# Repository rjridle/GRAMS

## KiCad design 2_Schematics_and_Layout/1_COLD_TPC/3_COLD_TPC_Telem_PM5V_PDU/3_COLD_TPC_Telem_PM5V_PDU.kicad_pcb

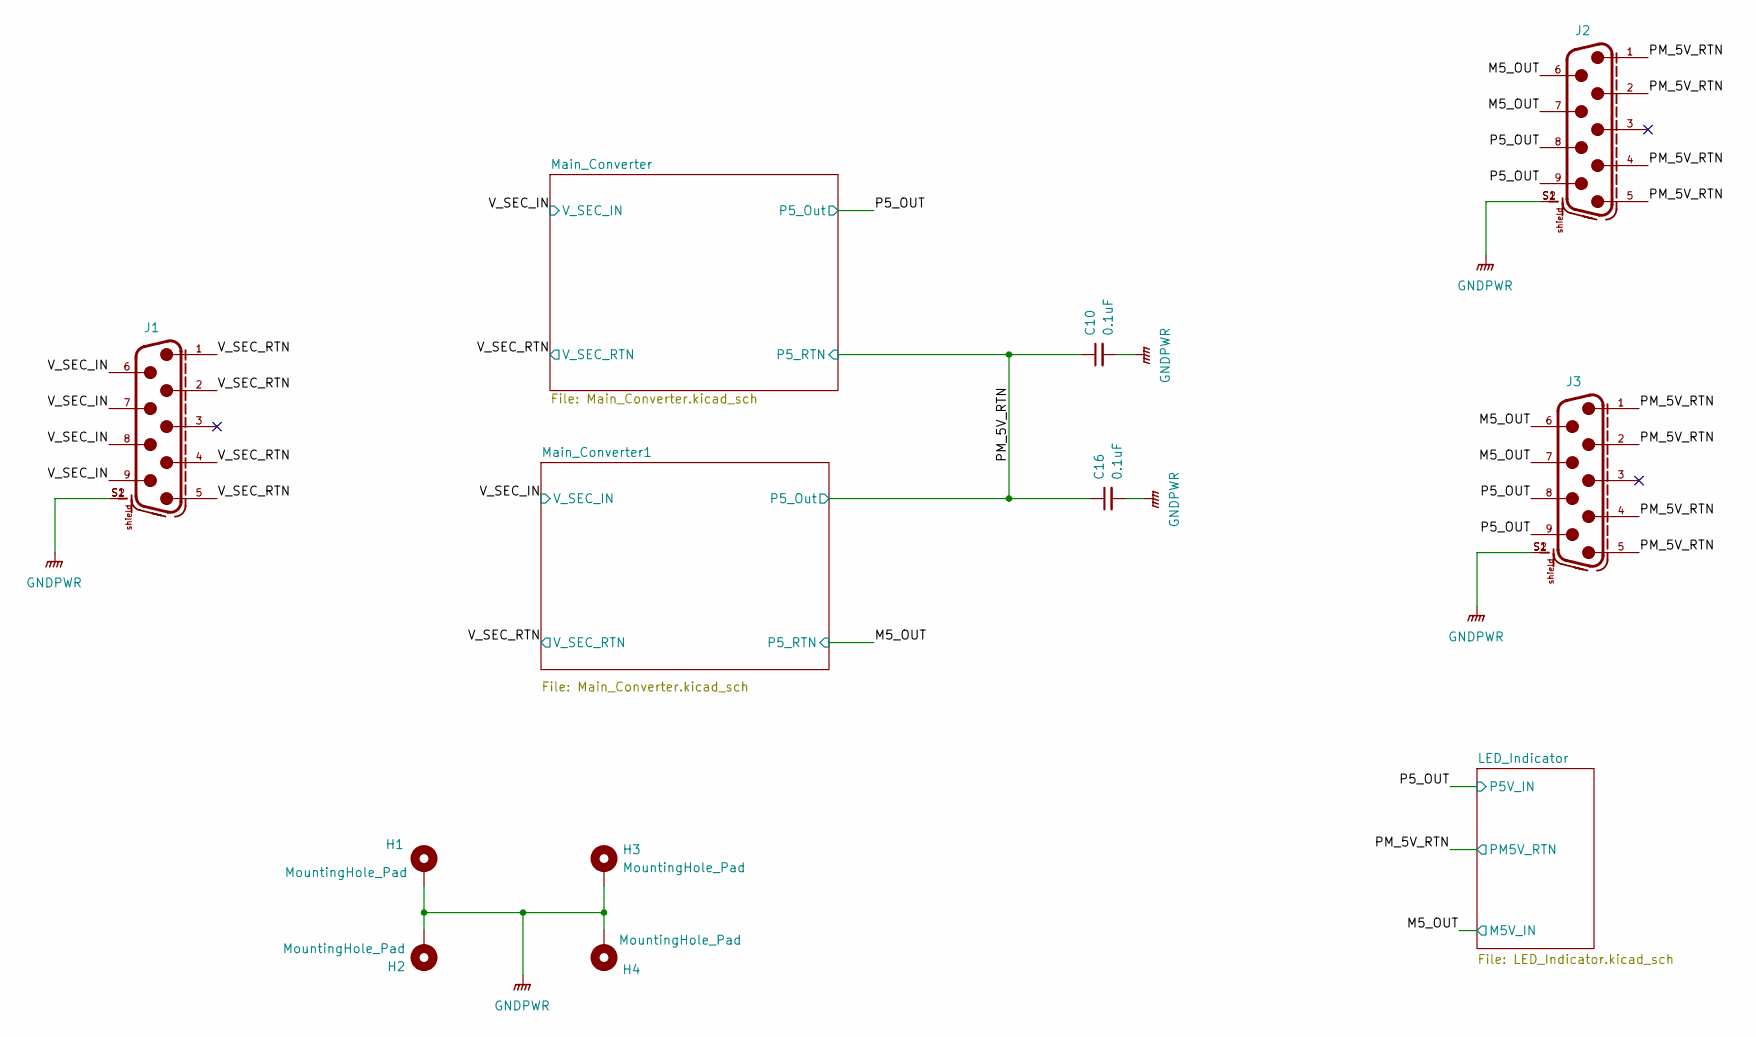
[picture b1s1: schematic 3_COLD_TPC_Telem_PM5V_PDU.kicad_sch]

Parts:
C10, C16: 0.1uF; C_0603_1608Metric; Man. Part Num CC0603KRX7R7BB104
H1, H2, H3, H4: MountingHole_Pad; MountingHole_3.2mm_M3_Pad
J1, J2, J3: 618009231221; PART-NUMBER 618009231221

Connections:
/M5_OUT: J2.6, J2.7, J3.6, J3.7; also elsewhere on the board
/P5_OUT: J2.8, J2.9, J3.8, J3.9; also elsewhere on the board
/PM_5V_RTN: C10.1, C16.1, J2.1, J2.2, J2.4, J2.5, J3.1, J3.2, J3.4, J3.5; also elsewhere on the board
/V_SEC_IN: J1.6, J1.7, J1.8, J1.9; also elsewhere on the board
/V_SEC_RTN: J1.1, J1.2, J1.4, J1.5; also elsewhere on the board
GNDPWR: C10.2, C16.2, H1.1, H2.1, H3.1, H4.1, J1.S1, J1.S2, J2.S1, J2.S2, J3.S1, J3.S2

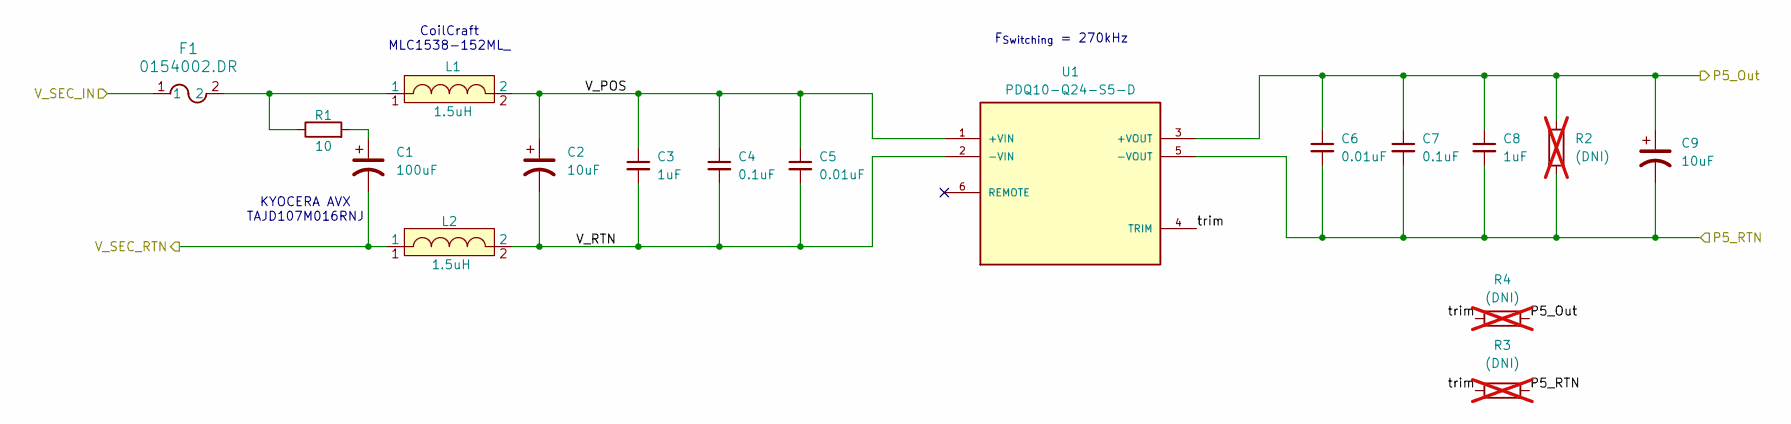
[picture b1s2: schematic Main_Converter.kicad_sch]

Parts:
C1: 100uF; CP_EIA-7343-20_Kemet-V; Man. Part Num TAJD107K020RNJ
C2: 10uF; CP_EIA-3216-12_Kemet-S; Man. Part Num TAJA106K016RNJ
C3, C8: 1uF; C_0603_1608Metric; Man. Part Num TMK107B7105KA-T
C4, C7: 0.1uF; C_0603_1608Metric; Man. Part Num CC0603KRX7R7BB104
C5, C6: 0.01uF; C_0603_1608Metric; Man. Part Num CL10B103KB8NNNC
C9: 10uF; CP_EIA-3216-10_Kemet-I; Man. Part Num T491A106M016AT
F1: 0154002.DR; 0154Series_LTF; Man. Part Num 0154002.DR
L1, L2: 1.5uH; MLC1538-; Man. Part Num MLC1538-152M
R1: 10; R_0805_2012Metric; Man. Part Num PCAN0805E10R0BST5
R2, R3, R4: (DNI); R_0805_2012Metric; not fitted
U1: PDQ10-Q24-S5-D; CONV_PDQ30-Q24-S5-D; PARTREV 1.0

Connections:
/Main_Converter/V_POS: C2.1, C3.1, C4.1, C5.1, L1.2, U1.1 (+VIN)
/Main_Converter/V_RTN: C2.2, C3.2, C4.2, C5.2, L2.2, U1.2 (-VIN)
/Main_Converter/trim: R3.1, R4.1, U1.4 (TRIM)
/P5_OUT: C6.1, C7.1, C8.1, C9.1, R2.1, R4.2, U1.3 (+VOUT); also elsewhere on the board
/PM_5V_RTN: C6.2, C7.2, C8.2, C9.2, R2.2, R3.2, U1.5 (-VOUT); also elsewhere on the board
/V_SEC_IN: F1.1; also elsewhere on the board
/V_SEC_RTN: C1.2, L2.1; also elsewhere on the board
unnamed: C1.1, R1.2
unnamed: F1.2, L1.1, R1.1

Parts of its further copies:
C11: 100uF; CP_EIA-7343-20_Kemet-V; Man. Part Num TAJD107K020RNJ
C12: 10uF; CP_EIA-3216-12_Kemet-S; Man. Part Num TAJA106K016RNJ
C13, C19: 1uF; C_0603_1608Metric; Man. Part Num TMK107B7105KA-T
C14, C18: 0.1uF; C_0603_1608Metric; Man. Part Num CC0603KRX7R7BB104
C15, C17: 0.01uF; C_0603_1608Metric; Man. Part Num CL10B103KB8NNNC
C20: 10uF; CP_EIA-3216-10_Kemet-I; Man. Part Num T491A106M016AT
F2: 0154002.DR; 0154Series_LTF; Man. Part Num 0154002.DR
L3, L4: 1.5uH; MLC1538-; Man. Part Num MLC1538-152M
R5: 10; R_0805_2012Metric; Man. Part Num PCAN0805E10R0BST5
R6, R7, R8: (DNI); R_0805_2012Metric; not fitted
U2: PDQ10-Q24-S5-D; CONV_PDQ30-Q24-S5-D; PARTREV 1.0

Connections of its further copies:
/M5_OUT: C17.2, C18.2, C19.2, C20.2, R6.2, R8.2, U2.5 (-VOUT); also elsewhere on the board
/Main_Converter1/V_POS: C12.1, C13.1, C14.1, C15.1, L3.2, U2.1 (+VIN)
/Main_Converter1/V_RTN: C12.2, C13.2, C14.2, C15.2, L4.2, U2.2 (-VIN)
/Main_Converter1/trim: R6.1, R7.1, U2.4 (TRIM)
/PM_5V_RTN: C17.1, C18.1, C19.1, C20.1, R7.2, R8.1, U2.3 (+VOUT); also elsewhere on the board
/V_SEC_IN: F2.1; also elsewhere on the board
/V_SEC_RTN: C11.2, L4.1; also elsewhere on the board
unnamed: C11.1, R5.2
unnamed: F2.2, L3.1, R5.1

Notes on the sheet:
CoilCraft MLC1538-152ML_
F_{Switching} = 270kHz
KYOCERA AVX TAJD107M016RNJ

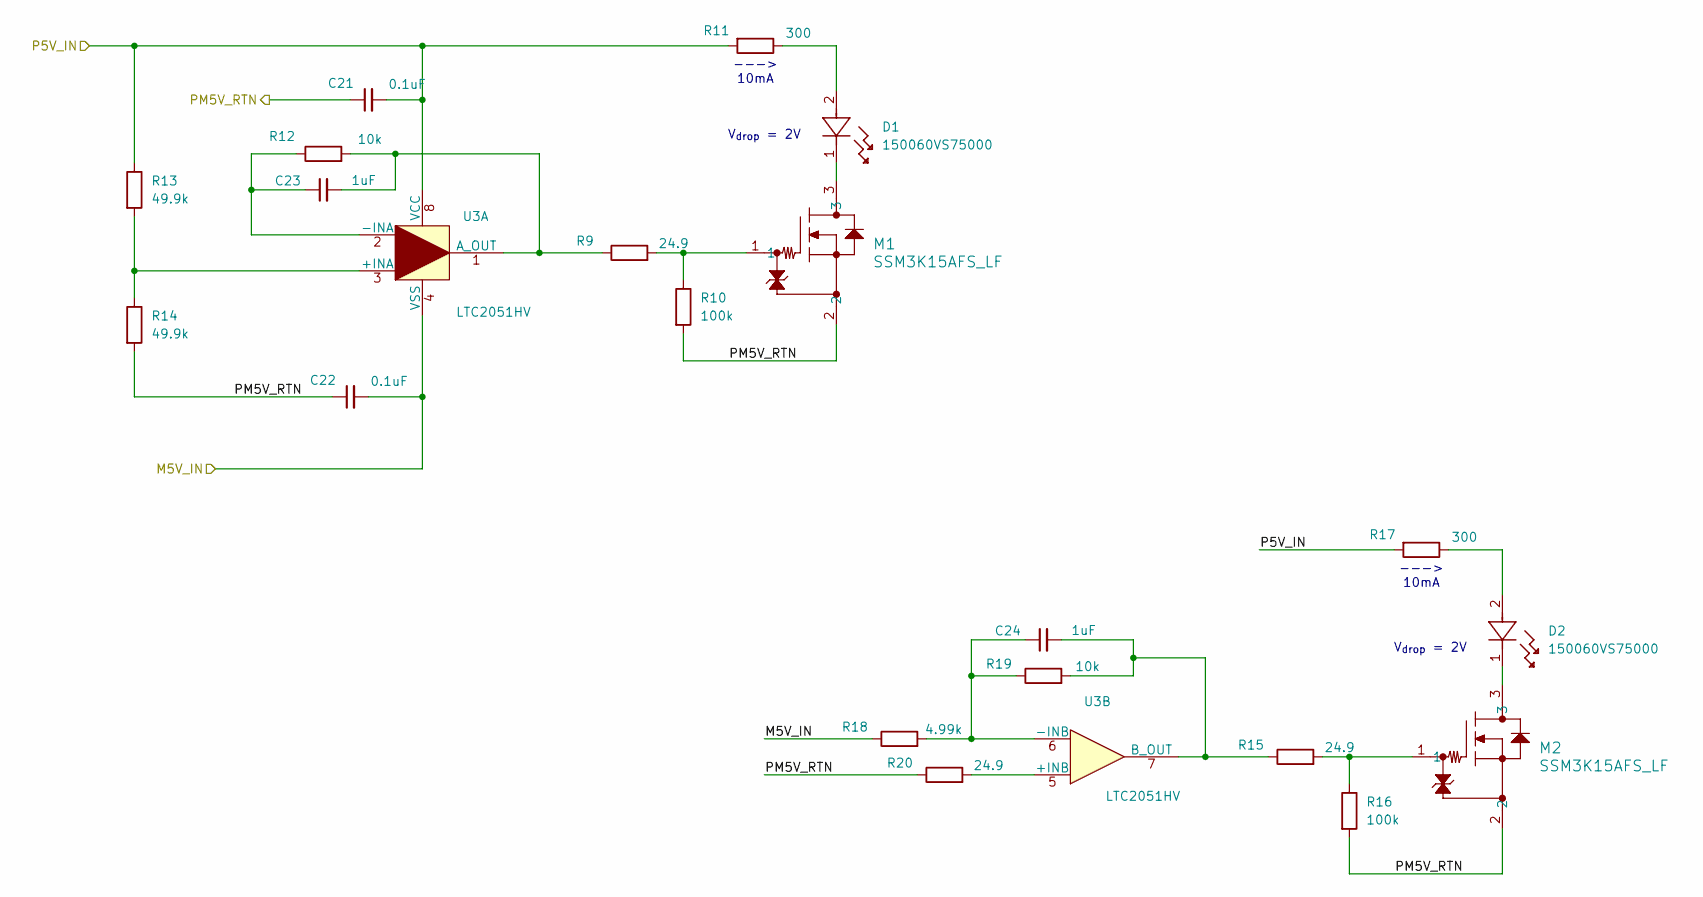
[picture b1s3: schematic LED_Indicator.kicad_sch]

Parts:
C21, C22: 0.1uF; C_0603_1608Metric; Man. Part Num CC0603KRX7R7BB104
C23, C24: 1uF; C_0402_1005Metric; Man. Part Num C0402C105K4PACTU
D1, D2: 150060VS75000; LED_0AS75000_WRE; Man. Part Num 150060AS75000
M1, M2: SSM3K15AFS_LF; SSM_TOS; Man. Part Num SSM3K15AFS,LF
R9, R15, R20: 24.9; R_0603_1608Metric; Man. Part Num RNCF0603TKY24R9
R10, R16: 100k; R_0603_1608Metric; Man. Part Num ERA-3AEB104V
R11, R17: 300; R_0603_1608Metric; Man. Part Num RT0603FRE07300RL
R12: 10k; R_0402_1005Metric; Man. Part Num ERA-2AEB103X
R13, R14: 49.9k; R_0603_1608Metric; Man. Part Num CPF0603F49K9C1
R18: 4.99k; R_0603_1608Metric; Man. Part Num ERA-3AEB4991V
R19: 10k; C_0402_1005Metric; Man. Part Num ERA-2AEB103X
U3: LTC2051HV; R_8_ADI; Man. Part Num LTC2051HVCS8#TRPBF

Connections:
/M5_OUT: C22.2, R18.1, U3.4 (VSS); also elsewhere on the board
/P5_OUT: C21.2, R11.2, R13.1, R17.2, U3.8 (VCC); also elsewhere on the board
/PM_5V_RTN: C21.1, C22.1, M1.2, M2.2, R10.2, R14.2, R16.2, R20.1; also elsewhere on the board
unnamed: D1.1, M1.3
unnamed: D1.2, R11.1
unnamed: D2.1, M2.3
unnamed: D2.2, R17.1
unnamed: M1.1, R9.2, R10.1
unnamed: M2.1, R15.2, R16.1
unnamed: R13.2, R14.1, U3.3 (+INA)
unnamed: C23.1, R12.1, U3.2 (-INA)
unnamed: C23.2, R9.1, R12.2, U3.1 (A_OUT)
unnamed: R20.2, U3.5 (+INB)
unnamed: C24.1, R18.2, R19.1, U3.6 (-INB)
unnamed: C24.2, R15.1, R19.2, U3.7 (B_OUT)

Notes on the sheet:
---> 10mA
V_{drop} = 2V

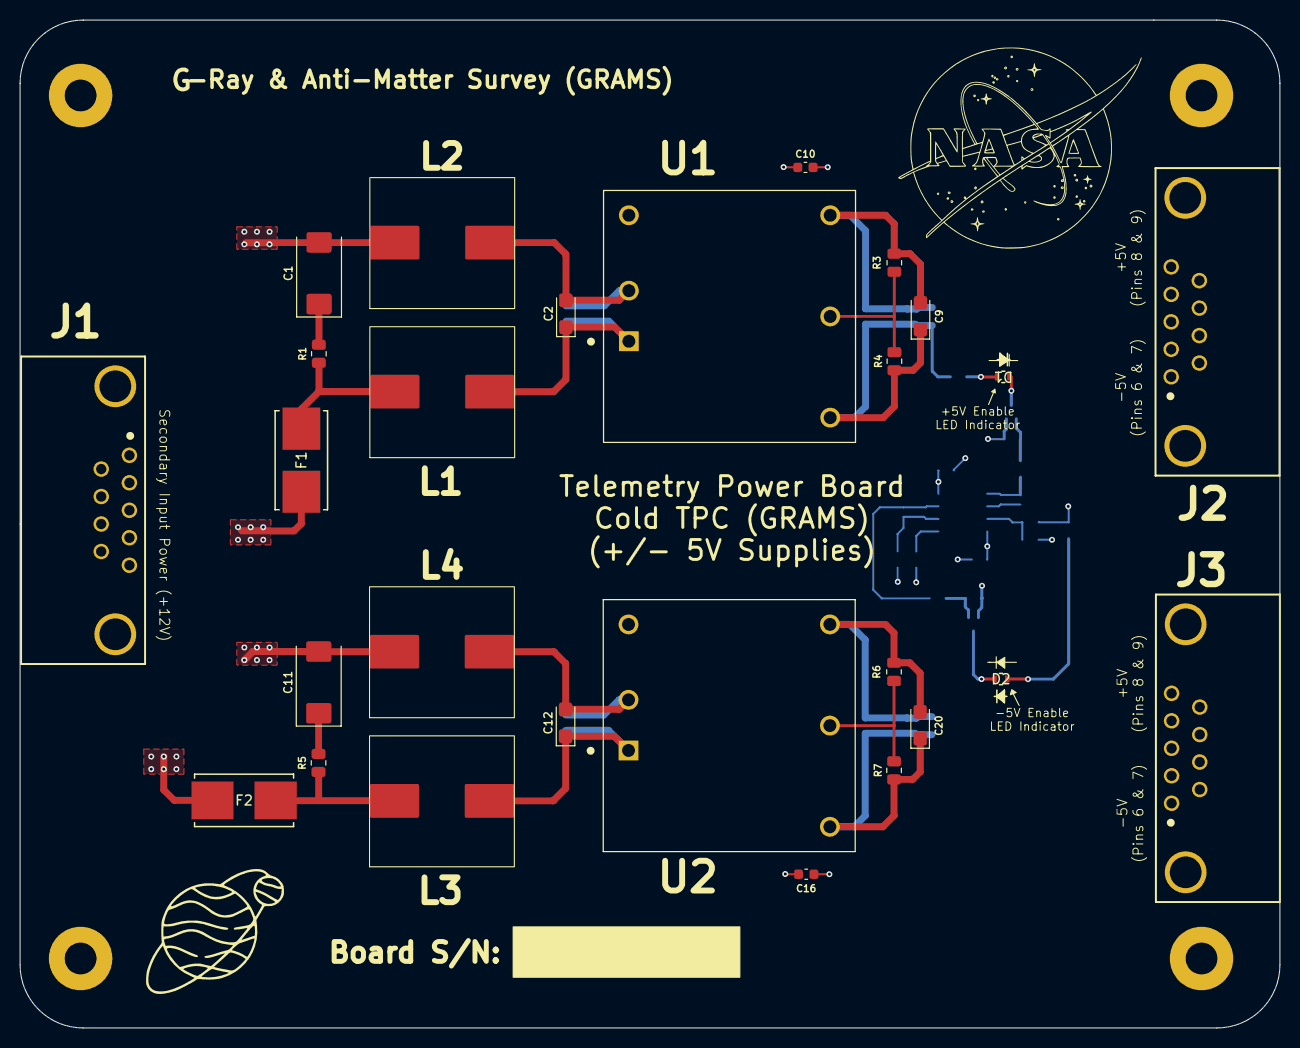
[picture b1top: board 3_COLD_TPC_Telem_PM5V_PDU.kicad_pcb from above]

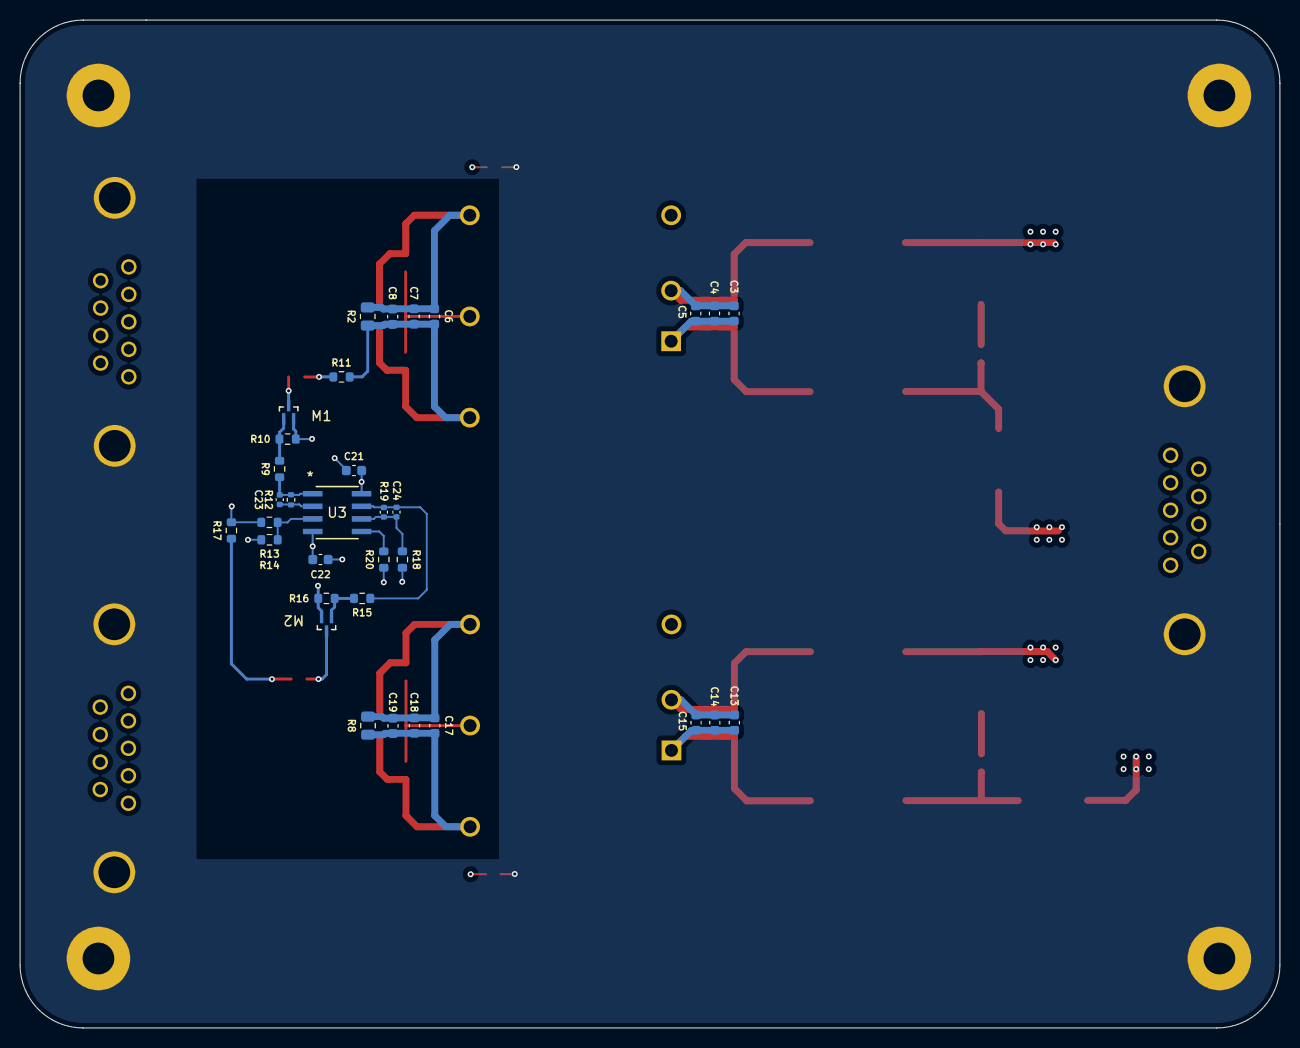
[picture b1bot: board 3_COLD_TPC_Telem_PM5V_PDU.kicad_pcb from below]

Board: 6 copper layers, 127.0 x 101.6 mm, 64 parts (33 on the bottom side), 28 nets.

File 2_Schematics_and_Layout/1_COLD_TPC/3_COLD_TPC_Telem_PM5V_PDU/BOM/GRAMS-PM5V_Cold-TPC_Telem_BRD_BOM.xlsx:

Item | Qty | REF DES | Manufacturer | Part Number |  |  |  | Description / Value | Package | Part Type | Notes
 |  |  |  | Manufacturer | Digi-Key | Mouser | Coil Craft
1 | 2 | C1,C11 | KYOCERA AVX | TAJD107M016RNJ | 478-3919-1-ND | - | - | 16V Tantalum, 100uF | 2917 | SMD | -
2 | 4 | C2,C9,C12,C20 | KEMET | T491A106K016AT | 399-8269-1-ND | - | - | 16V Tantalum, 10uF | 1206 | SMD | -
3 | 4 | C3,C8,C13,C19 | KEMET | C0603C105K4RACTU | 399-C0603C105K4RACTUCT-ND | - | - | Ceramic Capacitor, 1uF | 0603 | SMD | -
4 | 2 | C23, C24 | KYOCERA AVX | 0402ZD105KAT2A | 478-KGM05AR51A105KHCT-ND | - | - | Ceramic Capacitor, 1uF | 0402 | SMD | -
4 | 8 | C4,C7,C10,C14,C16,C18,C21,C22 | YAGEO | CC0603KRX7R7BB104 | 311-1088-1-ND | - | - | Ceramic Capacitor, 0.1uF | 0603 | SMD | -
5 | 4 | C5,C6,C15,C17 | Murata Electronics | GCM188R72A103KA37D | 490-4781-1-ND | - | - | Ceramic Capacitor, 0.01uF | 0603 | SMD | -
6 | 2 | D1,D2 | Würth Elektronik | 150060VS75000 | 732-4980-1-ND | - | - | Green 570nm LED | 0603 | SMD | -
7 | 2 | F1,F2
8 | 3 | J1,J2,J3 | Würth Elektronik | 618009231221 | 732-618009231221-ND | - | - | 9 P0S D-Sub Plug, Male Pins Con | - | Through Hole | -
9 | 4 | L1,L2,L3,L4 | Coil Craft | MLC1538-152ML_ | - | - | MLC1538-152ML_ | Inductors | - | SMD | -
10 | 2 | M1,M2 | Toshiba Semiconductor | SSM3K15AFS,LF | SSM3K15AFSLFCT-ND | - | - | N-Channel 3FET | - | SMD | -
11 | 2 | R1,R5 | YAGEO | RC0805FR-0710RL | 311-10.0CRCT-ND | - | - | 10-Ohm 0.125W Resistor | 0805 | SMD | -
12 | 6 | R2,R3,R4,R6,R7,R8 | DO NOT INSTALL
13 | 3 | R9,R15,R20 | YAGEO | RC0603FR-0724R9L | 311-24.9HRCT-ND | - | - | 24.9 Ohm Resistor (0.1W) | 0603 | SMD | -
14 | 2 | R10,R16 | Vishay Dale | CRCW0603100KFKEA | 541-100KHCT-ND | - | - | 100K-Ohm Resistor (0.1W) | 0603 | SMD | -
15 | 2 | R11,R17 | YAGEO | RC0603JR-07300RL | 311-300GRCT-ND | - | - | 300-Ohm Resistor (0.1W) | 0603 | SMD | -
16 | 2 | R12,R19 | YAGEO | RC0402JR-0710KL | 311-10KJRCT-ND | - | - | 10k-Ohm resistor (1/16W) | 0402 | SMD | -
17 | 2 | R13,R14 | YAGEO | RT0603BRD0750KL | 13-RT0603BRD0750KLCT-ND | - | - | 50k-Ohm resistor (0.1W) | 0603 | SMD | -
18 | 1 | R18 | YAGEO | RT0603BRE075KL | 13-RT0603BRE075KLCT-ND | - | - | 5k-Ohm resistor (0.1W) | 0603 | SMD | -
19 | 2 | U1,U2 | CUI Inc. | PDQ30-Q24-S5-D | 102-3891-ND | - | - | Isolated DC DC Converter 5V, 6A | - | Through Hole | -
20 | 1 | U3 | Analog Devices | LTC2051HVCS8#TRPBF | LTC2051HVCS8#TRPBFCT-ND | - | - | Chopper 0-Drift Dual Amp | 8-SOIC | SMD | -

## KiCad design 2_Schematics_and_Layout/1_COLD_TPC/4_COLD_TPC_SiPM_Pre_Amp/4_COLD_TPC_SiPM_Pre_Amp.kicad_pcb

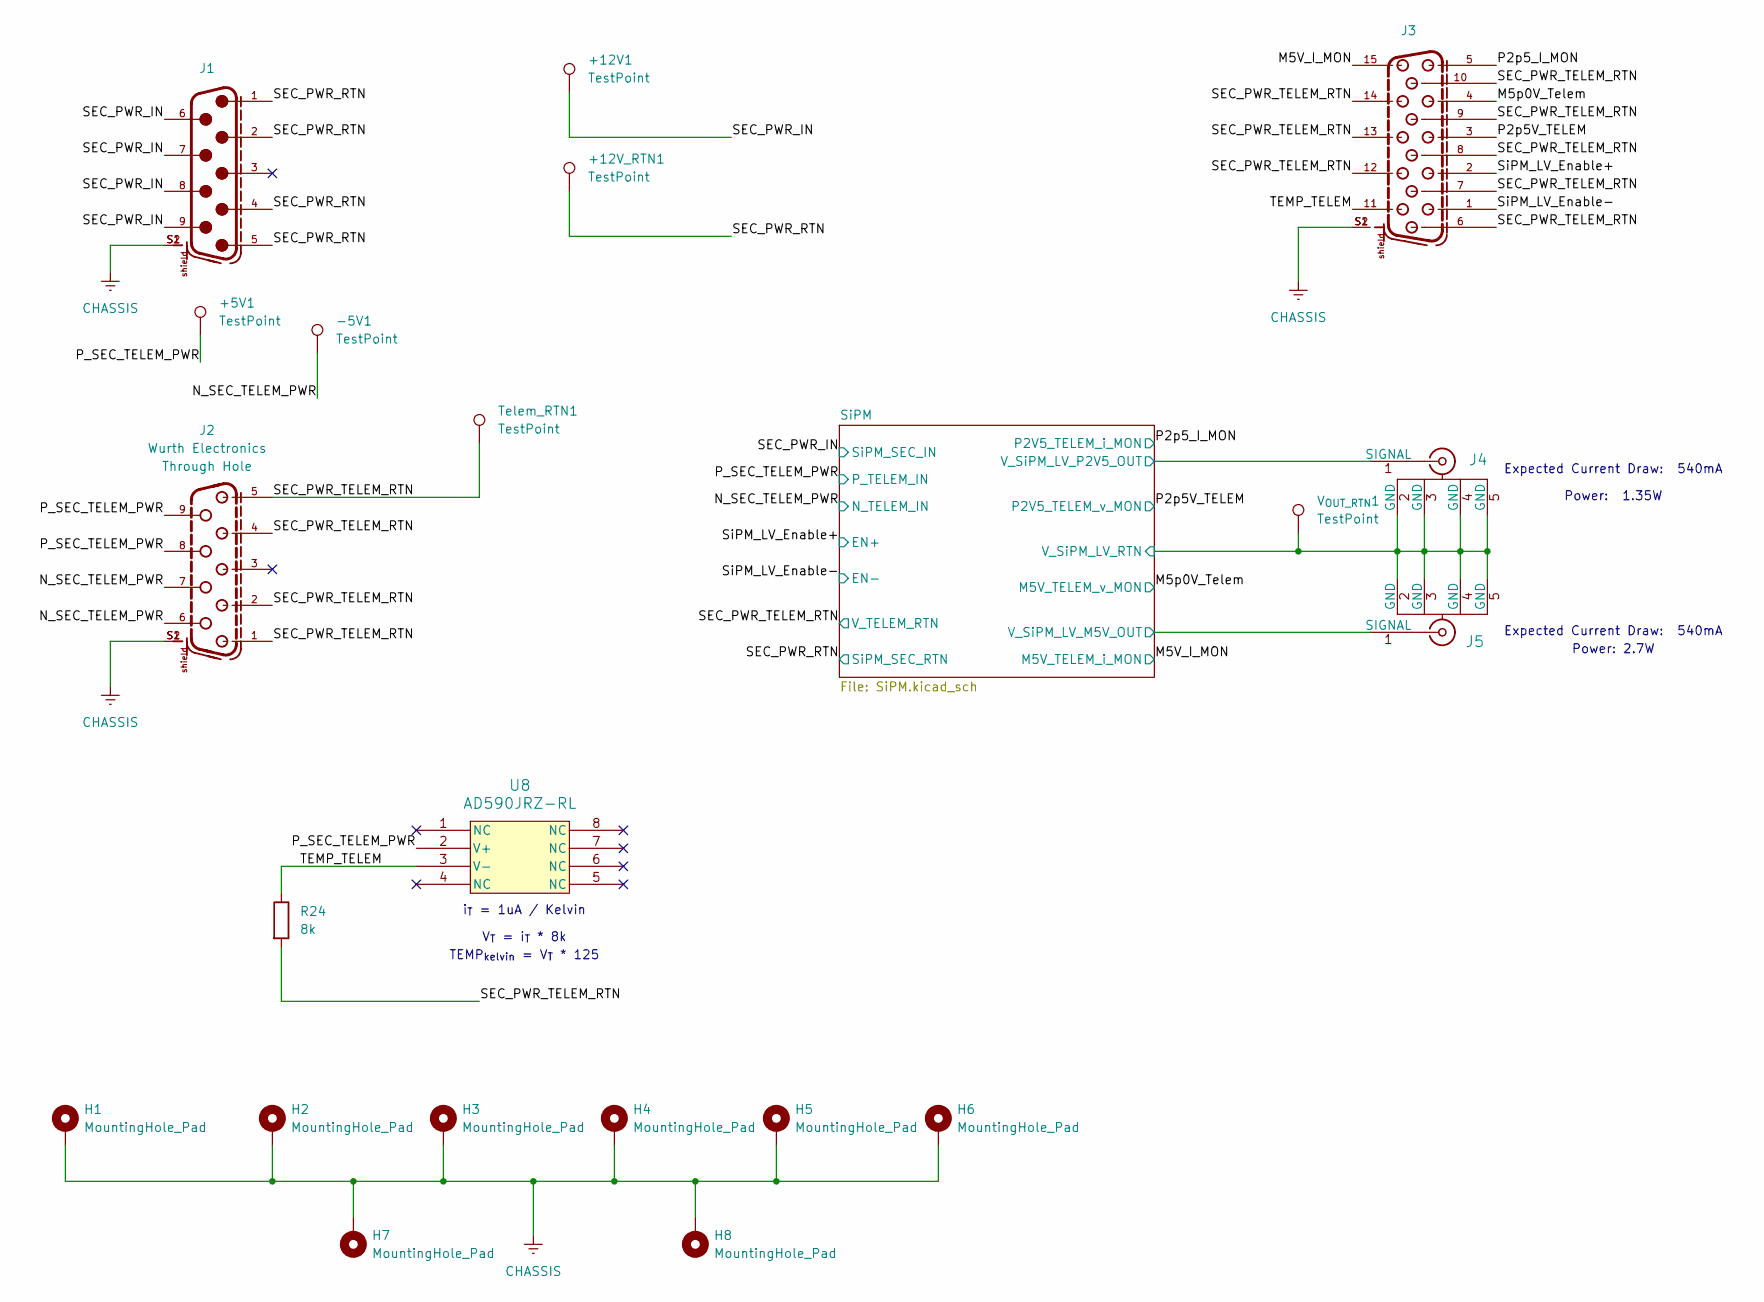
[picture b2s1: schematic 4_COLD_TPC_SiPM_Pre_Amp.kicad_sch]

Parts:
+5V1, +12V1: TestPoint; TestPoint_Keystone_5005-5009_Compact; Man. Part Num 5005
+12V_RTN1: TestPoint; TestPoint_Keystone_5005-5009_Compact; Man. Part Num 5006
-5V1: TestPoint; TestPoint_Keystone_5005-5009_Compact; Part Type Through Hole
H1, H2, H3, H4, H5, H6, H7, H8: MountingHole_Pad; MountingHole_3.2mm_M3_Pad
J1: 618009231221; PART-NUMBER 618009231221
J2: 618009231121; PART-NUMBER 618009231121
J3: 618015330923; PART-NUMBER 618015330923
J4, J5: RF2-49B-T-00-50-G-HDW; CONN_RF2-49B-T-00-50-G-HDW_ADM; Man. Part Num RF2-49B-T-00-50-G-HDW
R24: 8k; R_0603_1608Metric; Part Type SMD
Telem_RTN1: TestPoint; TestPoint_Keystone_5005-5009_Compact; Man. Part Num 5006
U8: AD590JRZ-RL; R_8_ADI; Man. Part Num AD590JRZ
V_{OUT_RTN}1: TestPoint; TestPoint_Keystone_5005-5009_Compact; Man. Part Num 5006

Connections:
/M5V_I_MON: J3.15; also elsewhere on the board
/M5p0V_Telem: J3.4; also elsewhere on the board
/N_SEC_TELEM_PWR: -5V1.1, J2.6, J2.7; also elsewhere on the board
/P2p5V_TELEM: J3.3; also elsewhere on the board
/P2p5_I_MON: J3.5; also elsewhere on the board
/P_SEC_TELEM_PWR: +5V1.1, J2.8, J2.9, U8.2 (V+); also elsewhere on the board
/SEC_PWR_IN: +12V1.1, J1.6, J1.7, J1.8, J1.9; also elsewhere on the board
/SEC_PWR_RTN: +12V_RTN1.1, J1.1, J1.2, J1.4, J1.5; also elsewhere on the board
/SEC_PWR_TELEM_RTN: J2.1, J2.2, J2.4, J2.5, J3.6, J3.7, J3.8, J3.9, J3.10, J3.12, J3.13, J3.14, R24.2, Telem_RTN1.1; also elsewhere on the board
/SiPM/SiPM_LV_Supply/SiPM_LV_5V/V_P5V_OUT: J4.2 (GND), J4.3 (GND), J4.4 (GND), J4.5 (GND), J5.2 (GND), J5.3 (GND), J5.4 (GND), J5.5 (GND), V_{OUT_RTN}1.1; also elsewhere on the board
/SiPM/V_SiPM_LV_M5V_OUT: J5.1 (SIGNAL); also elsewhere on the board
/SiPM/V_SiPM_LV_P2V5_OUT: J4.1 (SIGNAL); also elsewhere on the board
/SiPM_LV_Enable+: J3.2; also elsewhere on the board
/SiPM_LV_Enable-: J3.1; also elsewhere on the board
/TEMP_TELEM: J3.11, R24.1, U8.3 (V-)
CHASSIS: H1.1, H2.1, H3.1, H4.1, H5.1, H6.1, H7.1, H8.1, J1.S1, J1.S2, J2.S1, J2.S2, J3.S1, J3.S2; also elsewhere on the board

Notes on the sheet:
Expected Current Draw: 540mA
TEMP_{kelvin} = V_{T} * 125
Power: 1.35W
i_{T} = 1uA / Kelvin
V_{T} = i_{T} * 8k
Power: 2.7W

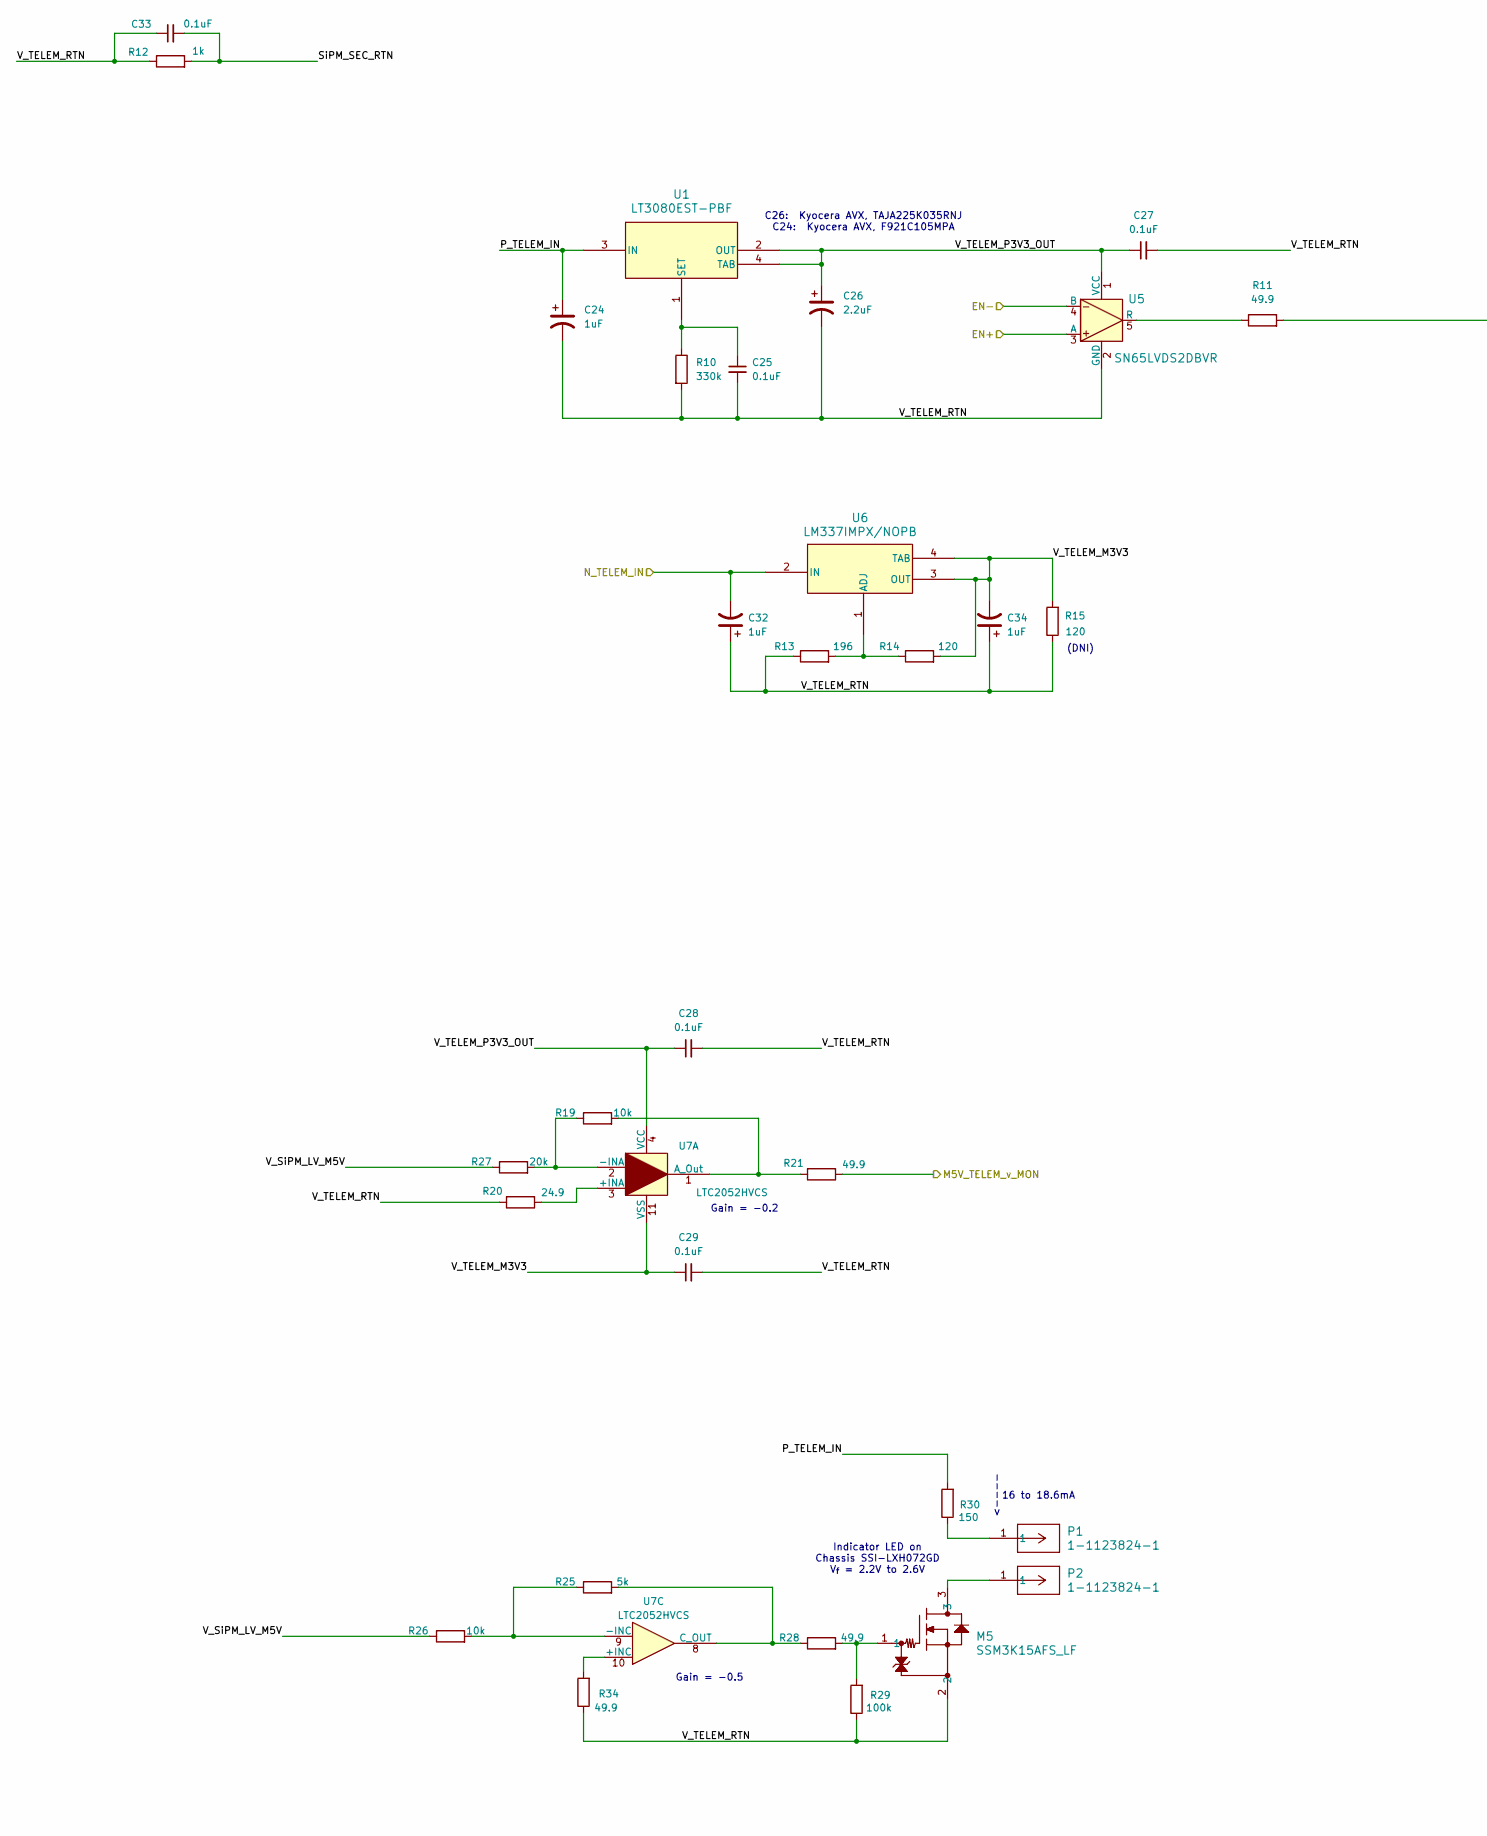
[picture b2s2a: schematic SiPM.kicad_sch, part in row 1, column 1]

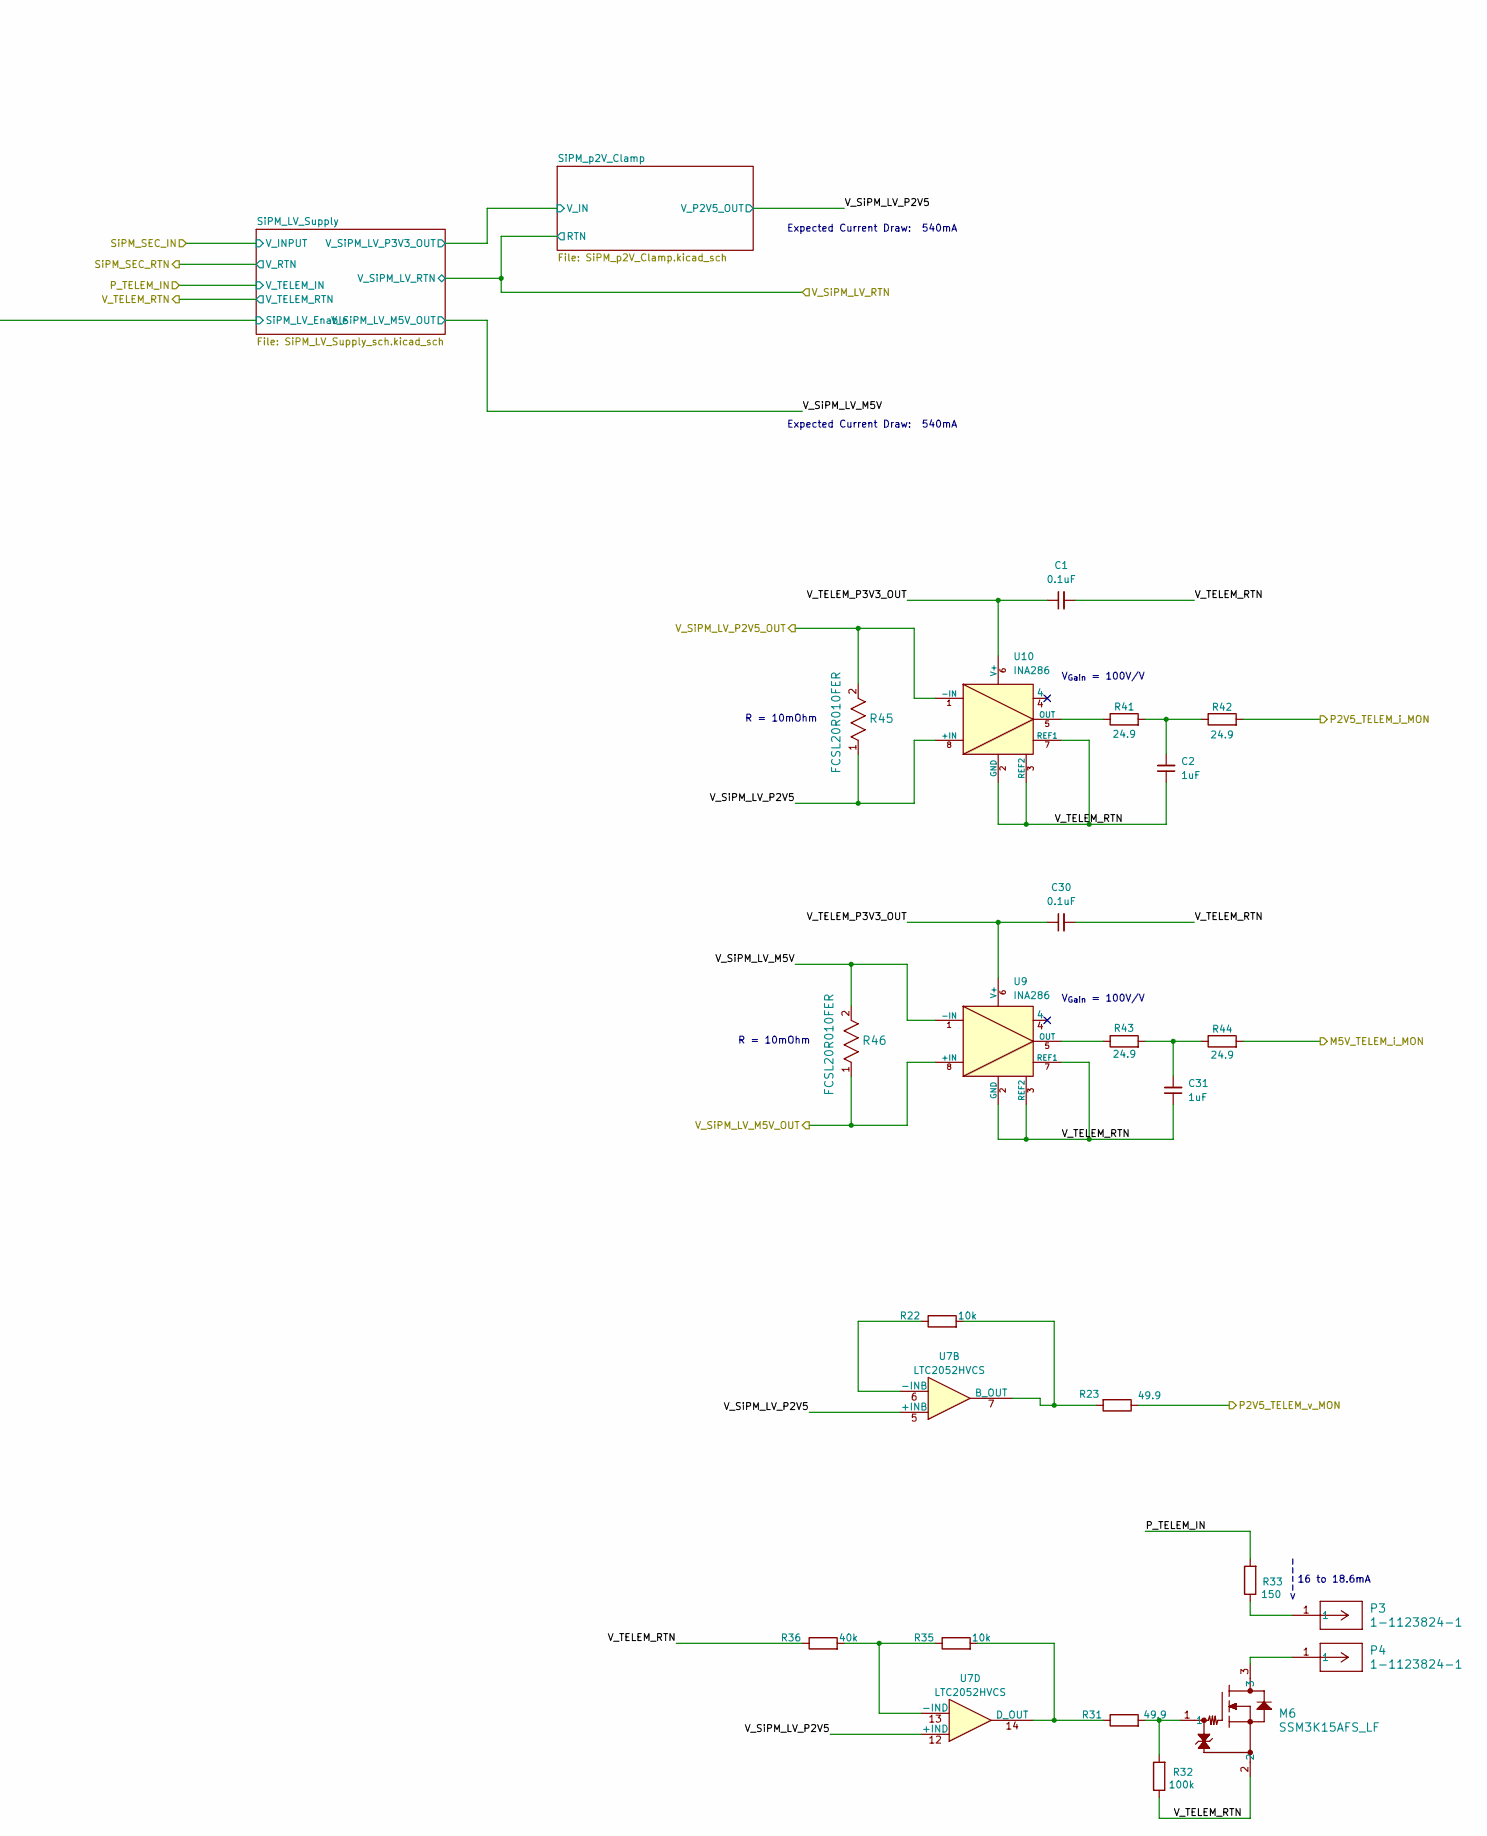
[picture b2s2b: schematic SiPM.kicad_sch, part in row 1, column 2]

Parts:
C1, C25, C27, C28, C29, C30, C33: 0.1uF; C_0603_1608Metric; Man. Part Num CC0603KRX7R7BB104
C2, C31: 1uF; C_0603_1608Metric; Man. Part Num CL10B105KO8NNNC
C24, C32, C34: 1uF; CP_EIA-2012-12_Kemet-R; Man. Part Num F921C105MPA
C26: 2.2uF; CP_EIA-3216-10_Kemet-I; Man. Part Num TAJA225K035RNJ
M5, M6: SSM3K15AFS_LF; SSM_TOS; Man. Part Num SSM3K15AFS,LF
P1, P2, P3, P4: 1-1123824-1; conn1_1-1123824-1_TEC; Man. Part Num 1-1123824-1
R10: 330k; R_0603_1608Metric; Part Type SMD
R11, R21, R23, R28, R31, R34: 49.9; R_0603_1608Metric; Part Type SMD
R12: 1k; R_0603_1608Metric; Man. Part Num RT0603BRD071KL
R13: 196; R_0603_1608Metric; Part Type SMD
R14, R15: 120; R_0603_1608Metric; Part Type SMD
R19, R22, R26, R35: 10k; R_0603_1608Metric; Part Type SMD
R20, R41, R42, R43, R44: 24.9; R_0603_1608Metric; Part Type SMD
R25: 5k; R_0603_1608Metric; Part Type SMD
R27: 20k; R_0603_1608Metric; Part Type SMD
R29, R32: 100k; R_0603_1608Metric; Part Type SMD
R30, R33: 150; R_0603_1608Metric; Part Type SMD
R36: 40k; R_0603_1608Metric; Part Type SMD
R45, R46: FCSL20R010FER; RES_FCSL20_OHM-L; Man. Part Num FCSL20R010FER
U1: LT3080EST-PBF; SOT-3_ST_LIT; Man. Part Num LT3080EST#PBF
U5: SN65LVDS2DBVR; DBV5; Man. Part Num SN65LVDS2DBVR
U6: LM337IMPX/NOPB; LM337IMPX; Man. Part Num LM337IMPX/NOPB
U7: LTC2052HVCS; SO-14_S_LIT; Man. Part Num LTC2052HVCS#PBF
U9, U10: INA286; SOIC127P599X175-8N; Man. Part Num INA286AIDR

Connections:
/M5V_I_MON: R44.2; also elsewhere on the board
/M5p0V_Telem: R21.1; also elsewhere on the board
/N_SEC_TELEM_PWR: C32.2, U6.2 (IN); also elsewhere on the board
/P2p5V_TELEM: R23.1; also elsewhere on the board
/P2p5_I_MON: R42.2; also elsewhere on the board
/P_SEC_TELEM_PWR: C24.1, R30.2, R33.2, U1.3 (IN); also elsewhere on the board
/SEC_PWR_RTN: C33.2, R12.2; also elsewhere on the board
/SEC_PWR_TELEM_RTN: C1.2, C2.1, C24.2, C25.2, C26.2, C27.2, C28.2, C29.2, C30.2, C31.1, C32.1, C33.1, C34.1, M5.2, M6.2, R10.2, R12.1, R13.1, R15.1, R20.2, R29.1, R32.1, R34.1, R36.1, U5.2 (GND), U9.2 (GND), U9.3 (REF2), U9.7 (REF1), U10.2 (GND), U10.3 (REF2), U10.7 (REF1); also elsewhere on the board
/SiPM/SiPM_LV_Supply/SiPM_LV_Enable: R11.2; also elsewhere on the board
/SiPM/V_SiPM_LV_M5V: R26.1, R27.1, R46.2, U9.1 (-IN); also elsewhere on the board
/SiPM/V_SiPM_LV_M5V_OUT: R46.1, U9.8 (+IN); also elsewhere on the board
/SiPM/V_SiPM_LV_P2V5: R45.1, U7.5 (+INB), U7.12 (+IND), U10.8 (+IN); also elsewhere on the board
/SiPM/V_SiPM_LV_P2V5_OUT: R45.2, U10.1 (-IN); also elsewhere on the board
/SiPM/V_TELEM_M3V3: C29.1, C34.2, R14.2, R15.2, U6.3 (OUT), U6.4 (TAB), U7.11 (VSS)
/SiPM/V_TELEM_P3V3_OUT: C1.1, C26.1, C27.1, C28.1, C30.1, U1.2 (OUT), U1.4 (TAB), U5.1 (VCC), U7.4 (VCC), U9.6 (V+), U10.6 (V+)
/SiPM_LV_Enable+: U5.3 (A); also elsewhere on the board
/SiPM_LV_Enable-: U5.4 (B); also elsewhere on the board
unnamed: C2.2, R41.2, R42.1
unnamed: C31.2, R43.2, R44.1
unnamed: M5.1, R28.2, R29.2
unnamed: M5.3, P2.1
unnamed: M6.1, R31.2, R32.2
unnamed: M6.3, P4.1
unnamed: P1.1, R30.1
unnamed: P3.1, R33.1
unnamed: C25.1, R10.1, U1.1 (SET)
unnamed: R11.1, U5.5 (R)
unnamed: R13.2, R14.1, U6.1 (ADJ)
unnamed: R20.1, U7.3 (+INA)
unnamed: R19.1, R27.2, U7.2 (-INA)
unnamed: R19.2, R21.2, U7.1 (A_Out)
unnamed: R22.1, U7.6 (-INB)
unnamed: R22.2, R23.2, U7.7 (B_OUT)
unnamed: R34.2, U7.10 (+INC)
unnamed: R25.1, R26.2, U7.9 (-INC)
unnamed: R25.2, R28.1, U7.8 (C_OUT)
unnamed: R35.1, R36.2, U7.13 (-IND)
unnamed: R31.1, R35.2, U7.14 (D_OUT)
unnamed: R43.1, U9.5 (OUT)
unnamed: R41.1, U10.5 (OUT)

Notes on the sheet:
R = 10mOhm
16 to 18.6mA
Expected Current Draw: 540mA
<----
(DNI)
V_{Gain} = 100V/V
Gain = -0.5
Gain = -0.2
C26: Kyocera AVX, TAJA225K035RNJ C24: Kyocera AVX, F921C105MPA
Indicator LED on Chassis SSI-LXH072GD V_{f} = 2.2V to 2.6V
